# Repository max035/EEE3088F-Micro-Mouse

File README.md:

# EEE3088F-Micro-Mouse

This project is made up of five modulues. Namely the mother board, the processor, power and sensing. We will be focusing on power and sensing.

## Sensing Subsystem

The sensing subsystem is a crucial component of the micro-mouse project, responsible for detecting walls and enabling the robot to navigate the maze effectively. This subsystem consists of three main components:

1. Emitter-Receiver (ER) Sensor Subsystem
2. Power Saving Mechanism
3. Output and Level Shifting

### Emitter-Receiver (ER) Sensor Subsystem

The ER sensor subsystem includes three separate ER circuits for left, front, and right wall detection. Each circuit utilizes a TSAL4400 IR emitting diode and an SFH203 photodiode. The emitter circuit is designed to provide the optimal current of 100mA to the IR emitting diode, while the receiver circuit uses a 100kΩ resistor in series with the photodiode for sensitive output.

### Power Saving Mechanism

To reduce power consumption, the sensing subsystem employs Pulse Width Modulation (PWM) to control the duty cycle of the ER circuits. PWM allows the ER sensors to operate for a shorter time while still functioning as intended, resulting in significant power savings compared to continuous operation.

### Output and Level Shifting

Initially, the analog output signals from the ER sensors were intended to be converted to digital levels using an NPN and PNP transistor-based level shifter. However, during testing, it was determined that connecting the analog outputs directly to the ADC pins of the microcontroller (PA4, PA5, PA6) provided a more adaptable and robust solution for handling variations in ambient light conditions.

### PCB Design

The sensing subsystem PCB has been designed to fit within the available space on the micro-mouse chassis, with a width less than 70mm and a length between 6mm and 50mm. The PCB includes strategically placed jumpers for debugging and test points for probing, facilitating easy troubleshooting and modification. The PCB connects to the motherboard via a 2x14 pin header.

### Acceptance Testing

The sensing subsystem has undergone rigorous acceptance testing to ensure its functionality, reliability, and compatibility with the micro-mouse platform. The testing procedures covered the following aspects:

1. Functionality test of the ER subsystems (AT-01)
2. Consistency test of the sensing subsystem's output voltage (AT-02)
3. Functionality test of the sensing subsystem software (AT-03)
4. Power consumption test of the sensing subsystem (AT-04)
5. Physical compatibility test (AT-05)

The results of the acceptance tests demonstrated the effectiveness of the design decisions and modifications made throughout the project, ensuring that the sensing subsystem meets the project's requirements and specifications.

For more detailed information on the sensing subsystem design, testing, and results, please refer to the [project report](/Sensing%20Subsystem/Write%20Up/EEE3088F_final_report.pdf).

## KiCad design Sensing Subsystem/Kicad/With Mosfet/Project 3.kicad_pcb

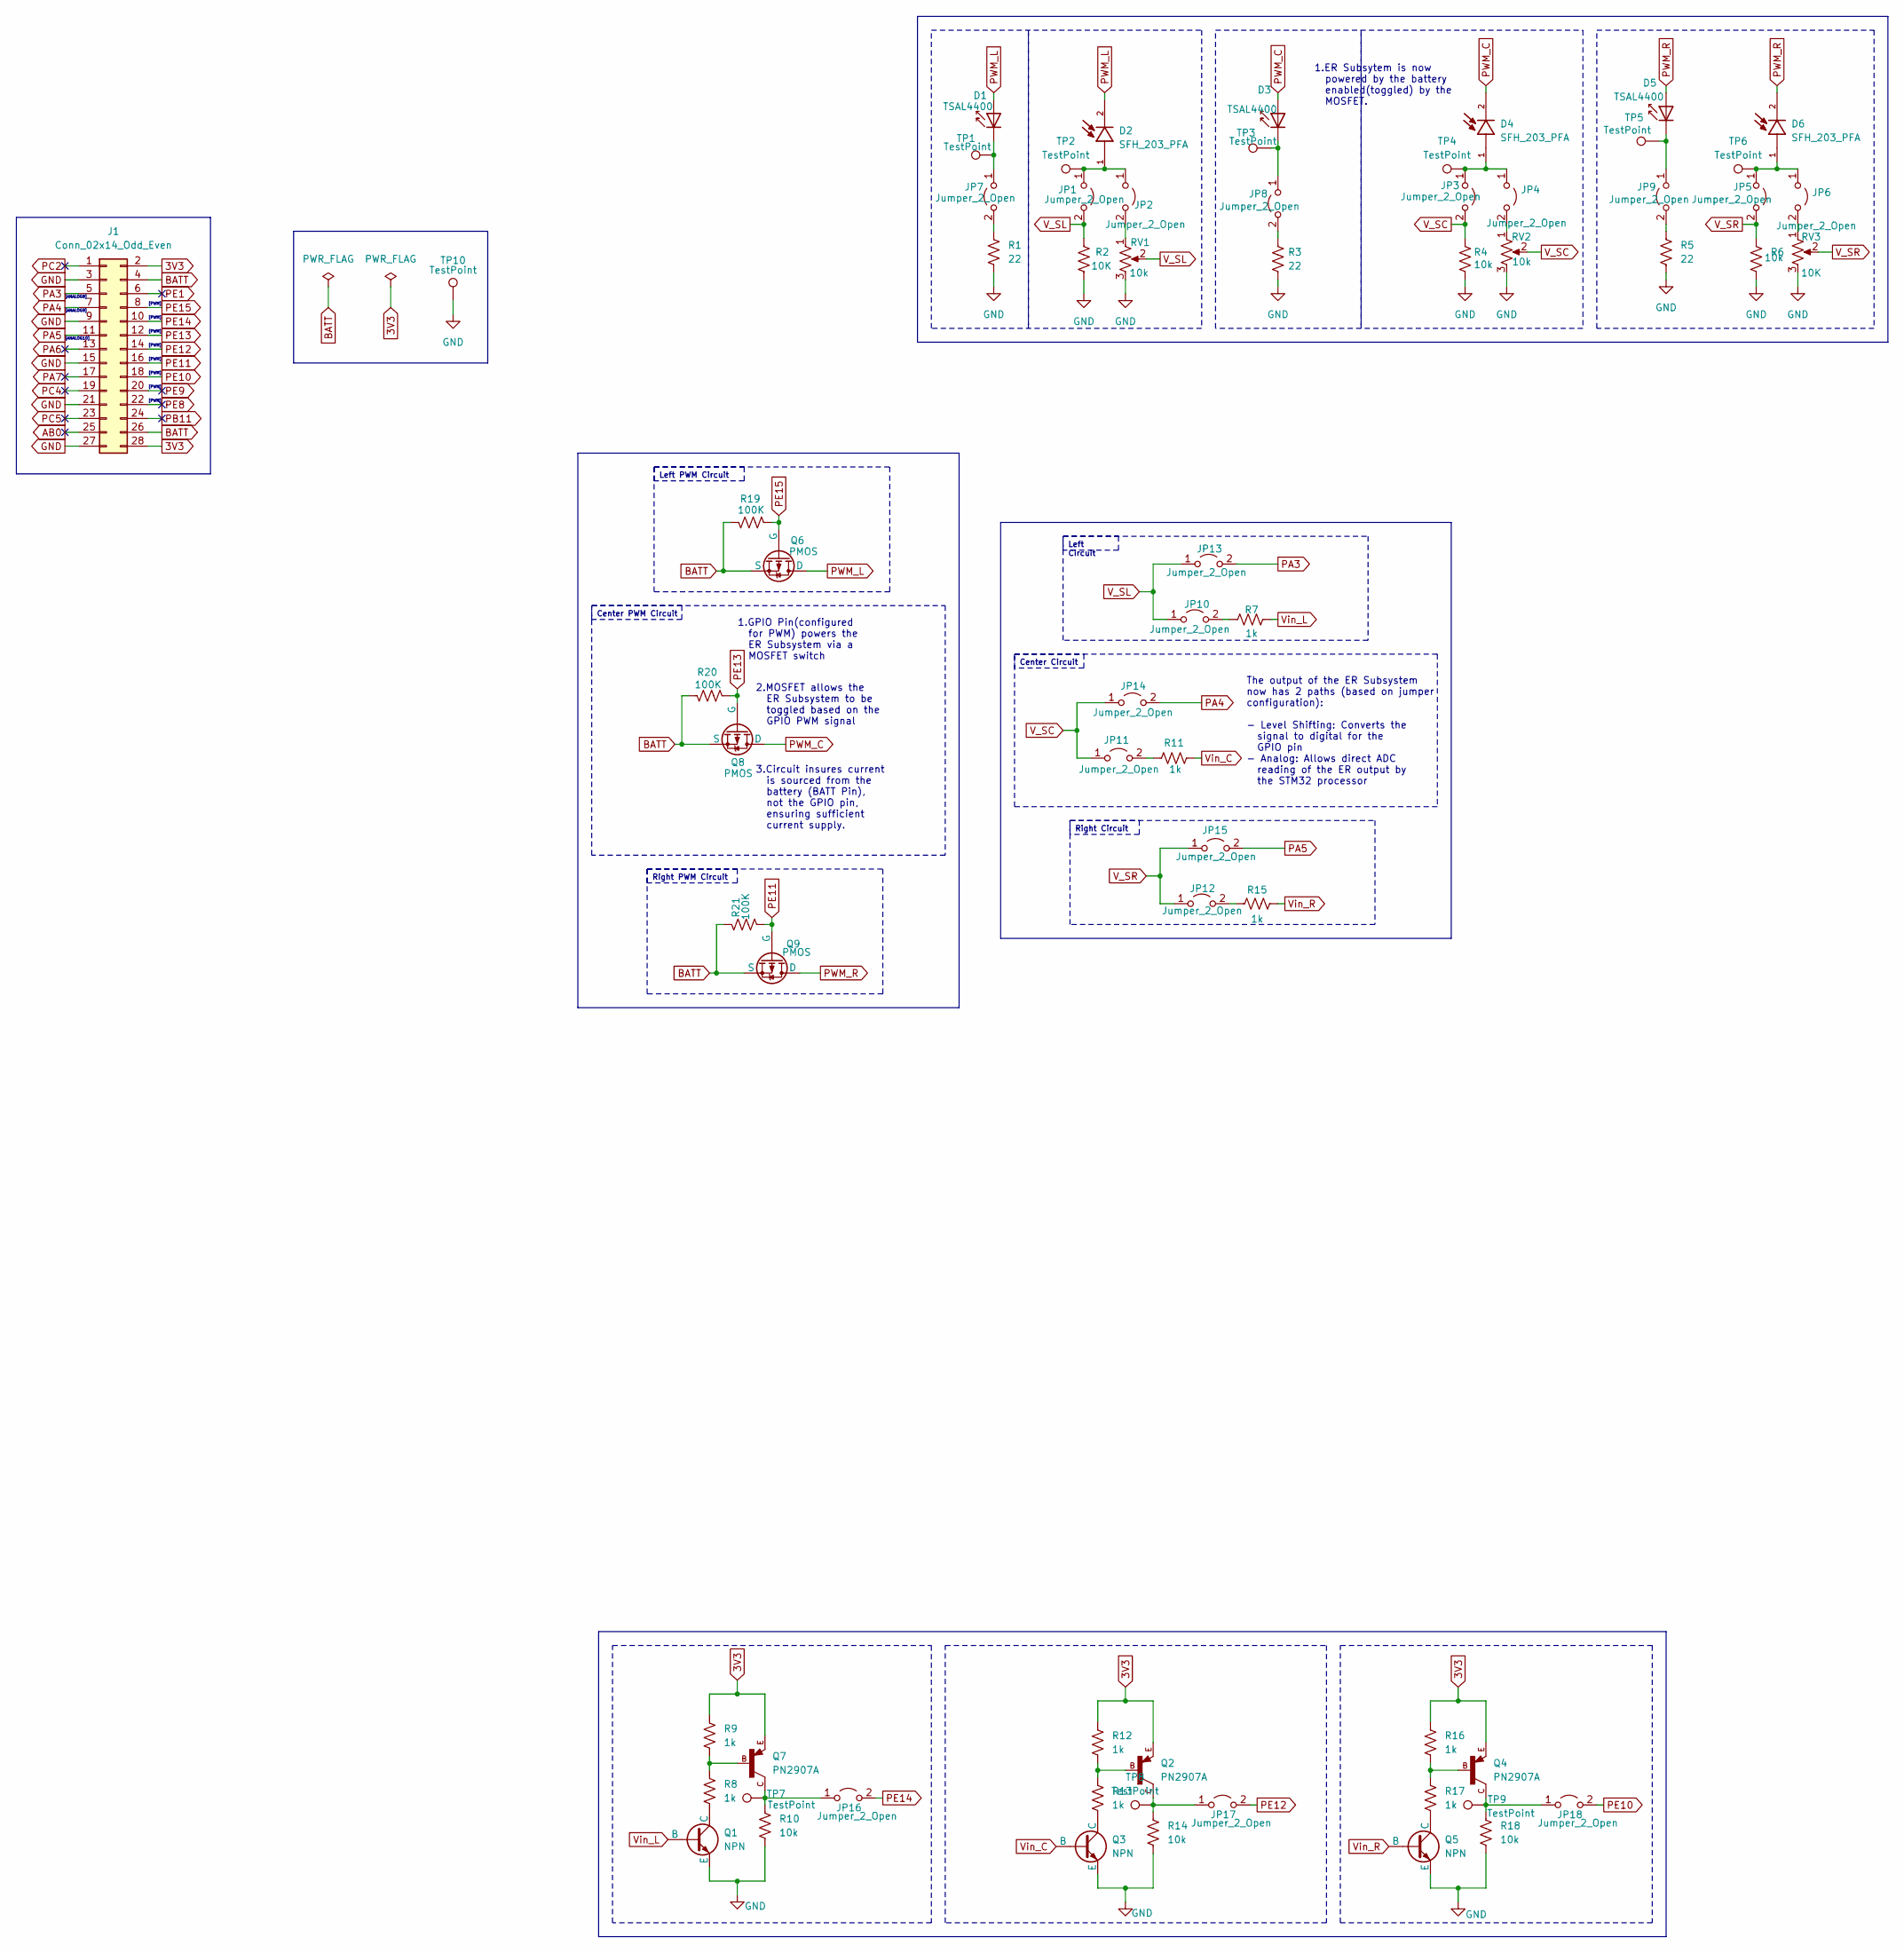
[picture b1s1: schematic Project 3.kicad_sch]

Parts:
D1, D3, D5: TSAL4400; LED_D3.0mm_Horizontal_O1.27mm_Z2.0mm_IRBlack
D2, D4, D6: SFH_203_PFA; XDCR_SFH_203_PFA; PARTREV 1.3
J1: Conn_02x14_Odd_Even; PinHeader_2x14_P2.54mm_Vertical
JP1, JP2, JP3, JP4, JP5, JP6, JP7, JP8, JP9, JP10, JP11, JP12, JP13, JP14, JP15, JP16, JP17, JP18: Jumper_2_Open; SolderJumper-2_P1.3mm_Open_Pad1.0x1.5mm
Q1, Q3, Q5: NPN; TO-92L
Q2, Q4, Q7: PN2907A; TO92-EBC
Q6, Q8, Q9: PMOS; SOT-23-3
R1, R3, R5: 22; R_0603_1608Metric
R2, R6: 10K; R_0603_1608Metric
R4, R10, R14, R18: 10k; R_0603_1608Metric
R7, R8, R9, R11, R12, R13, R15, R16, R17: 1k; R_0603_1608Metric
R19, R20, R21: 100K; R_0603_1608Metric
RV1, RV2, RV3: 10k; POT_3386P
TP1, TP2, TP3, TP4, TP5, TP6, TP7, TP8, TP9, TP10: TestPoint; TestPoint_Pad_D1.0mm

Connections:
3V3: J1.2, J1.28, Q2.E, Q4.E, Q7.E, R9.2, R12.2, R16.2
AB0: J1.25
BATT: J1.4, J1.26, Q6.3 (S), Q8.3 (S), Q9.3 (S), R19.2, R20.2, R21.2
GND: J1.3, J1.9, J1.15, J1.21, J1.27, Q1.3 (E), Q3.3 (E), Q5.3 (E), R1.1, R2.1, R3.1, R4.1, R5.1, R6.1, R10.1, R14.1, R18.1, RV1.3, RV2.3, RV3.3, TP10.1
unnamed: D1.2 (A), D2.2, Q6.1 (D)
unnamed: D1.1 (K), JP7.1 (A), TP1.1
unnamed: D3.2 (A), D4.2, Q8.1 (D)
unnamed: D3.1 (K), JP8.1 (A), TP3.1
unnamed: D5.2 (A), D6.2, Q9.1 (D)
unnamed: D2.1, JP1.1 (A), JP2.1 (A), TP2.1
unnamed: JP2.2 (B), RV1.1
unnamed: D4.1, JP3.1 (A), JP4.1 (A), TP4.1
unnamed: JP4.2 (B), RV2.1
unnamed: D6.1, JP5.1 (A), JP6.1 (A), TP6.1
unnamed: JP6.2 (B), RV3.1
unnamed: JP7.2 (B), R1.2
unnamed: JP8.2 (B), R3.2
unnamed: JP10.2 (B), R7.1
unnamed: JP11.2 (B), R11.1
unnamed: JP12.2 (B), R15.1
unnamed: JP16.1 (A), Q7.C, R10.2, TP7.1
unnamed: JP17.1 (A), Q2.C, R14.2, TP8.1
unnamed: JP18.1 (A), Q4.C, R18.2, TP9.1
unnamed: Q1.2 (B), R7.2
unnamed: Q1.1 (C), R8.1
unnamed: Q2.B, R12.1, R13.2
unnamed: Q3.2 (B), R11.2
unnamed: Q3.1 (C), R13.1
unnamed: Q4.B, R16.1, R17.2
unnamed: Q5.2 (B), R15.2
unnamed: Q5.1 (C), R17.1
unnamed: Q7.B, R8.2, R9.1
PA3: J1.5, JP13.2 (B)
PA4: J1.7, JP14.2 (B)
PA5: J1.11, JP15.2 (B)
PA6: J1.13
PA7: J1.17
PB11: J1.24
PC2: J1.1
PC4: J1.19
PC5: J1.23
PE1: J1.6
PE8: J1.22
PE9: J1.20
PE10: J1.18, JP18.2 (B)
PE11: J1.16, Q9.2 (G), R21.1
PE12: J1.14, JP17.2 (B)
PE13: J1.12, Q8.2 (G), R20.1
PE14: J1.10, JP16.2 (B)
PE15: J1.8, Q6.2 (G), R19.1
V_SC: JP3.2 (B), JP11.1 (A), JP14.1 (A), R4.2, RV2.2
V_SL: JP1.2 (B), JP10.1 (A), JP13.1 (A), R2.2, RV1.2
V_SR: JP5.2 (B), JP12.1 (A), JP15.1 (A), R6.2, RV3.2

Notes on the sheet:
Right PWM Circuit
Center PWM Circuit
Left PWM Circuit
Left Circuit
Center Circuit
Right Circuit
The output of the ER Subsystem now has 2 paths (based on jumper configuration): - Level Shifting: Converts the signal to digital for the GPIO pin - Analog: Allows direct ADC reading of the ER output by the STM32 processor
1.ER Subsytem is now powered by the battery enabled(toggled) by the MOSFET.
[PWM]
[ANALOG9]
3.Circuit insures current is sourced from the battery (BATT Pin), not the GPIO pin, ensuring sufficient current supply.
[ANALOG10]
1.GPIO Pin(configured for PWM) powers the ER Subsystem via a MOSFET switch
[ANALOG8]
2.MOSFET allows the ER Subsystem to be toggled based on the GPIO PWM signal

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
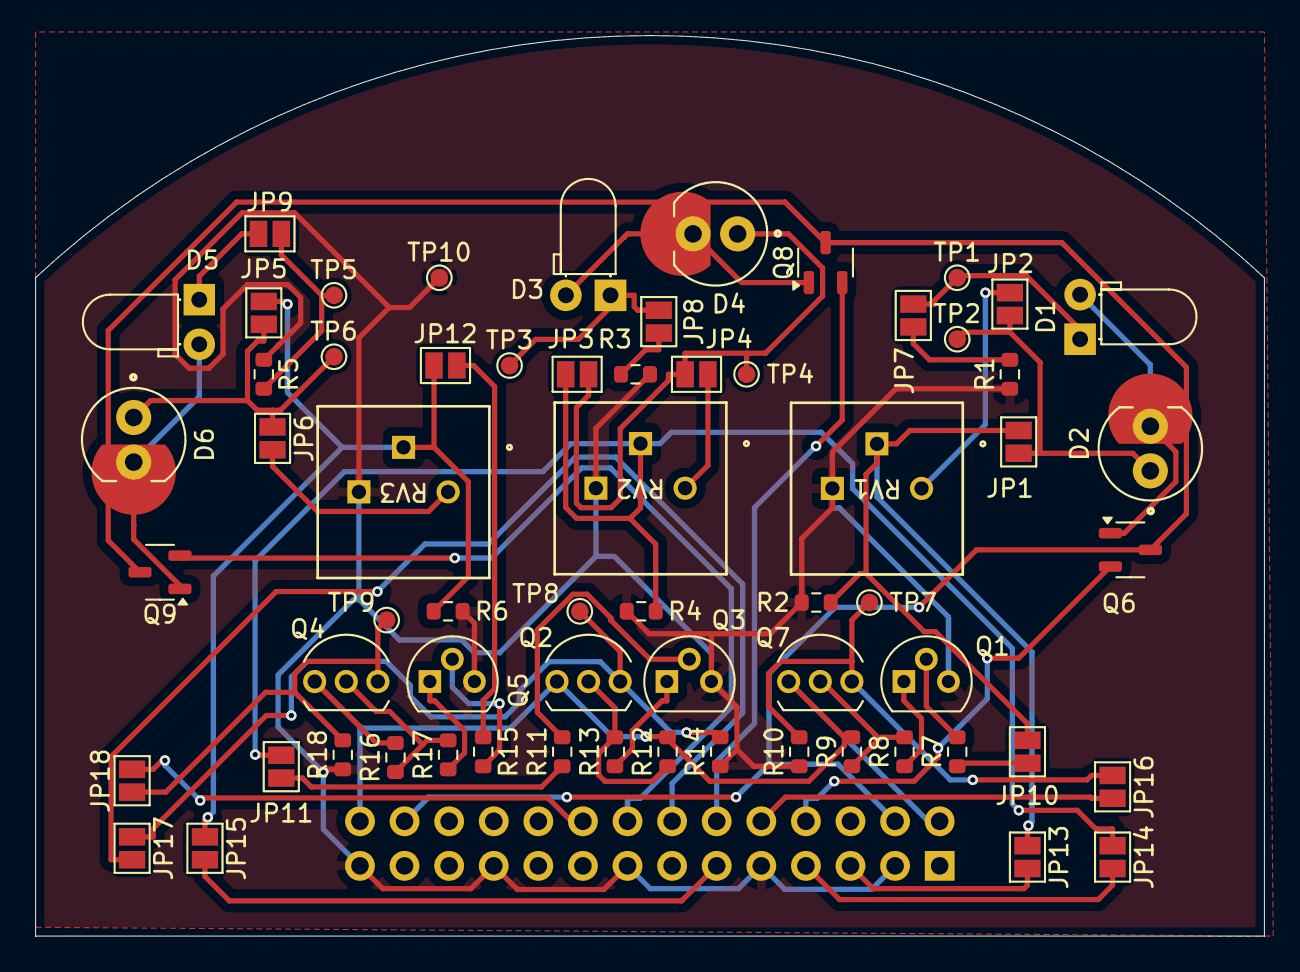
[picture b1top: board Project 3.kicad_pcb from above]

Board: 2 copper layers, 70.0 x 51.3 mm, 65 parts (1 on the bottom side), 45 nets.

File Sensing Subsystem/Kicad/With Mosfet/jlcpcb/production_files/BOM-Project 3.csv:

Comment,Designator,Footprint,LCSC
PMOS,"Q6,Q8,Q9",SOT-23-3,C15127
1k,"R11,R12,R13,R15,R16,R17,R7,R8,R9",R_0603_1608Metric,C23186
10k,"R10,R14,R18,R2,R4,R6",R_0603_1608Metric,C23192
100,"R1,R3,R5",R_0603_1608Metric,C23345
PN2907A,"Q2,Q4,Q7",TO92-EBC,C358534
NPN,"Q1,Q3,Q5",TO-92L,C5330385
SFH_203_PFA,"D2,D4,D6",XDCR_SFH_203_PFA,C554984
TSAL4400,"D1,D3,D5",LED_D3.0mm_Horizontal_O1.27mm_Z2.0mm_IRBlack,C94135
10k,RV2,POT_3386P,
10k,RV3,POT_3386P,
10k,RV1,POT_3386P,
Conn_02x14_Odd_Even,J1,PinHeader_2x14_P2.54mm_Vertical,

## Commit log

2024-04-16 Power subsystem files
2024-04-18 Create hello.txt
    This is a test
2024-04-21 Richards Folder
2024-04-21 Datasheets for other drivers and charging ICs
2024-05-18 Add ADC and PWM code
2024-05-18 Addition of: Sensing Subsystem Readme, Report Figures, Final Report markdown and PDF
2024-05-18 add link to report
2024-05-18 removed hello.txt
